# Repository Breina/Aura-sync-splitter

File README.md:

Aura sync splitter
===

Purpose
---
This schematic can be used for when one wants to use the an addressable WS2811B signal to power additional RGB components separately. These component groups will have their own dedicated PSU connection.

Setup
---
Include the `WS2811.lbr` library as a library in Eagle. This is the DIP8 version of the WS2811 IC.

Requirements
---

This board was made in Eagle, so it's a requirement to do anything with the source files. As for hardware, for one board, one needs:
* 8x WS2811 IC's, DIP8 format
* 9x 2.54 mm groups of 4 round pins.
* 9x 33 Ω resistors (R1 - R9) used to prevent reflection and hot-swap.
* 8x 100 nF capacitors used as bypass.
* Every connected component requires an additional resistor (RR0 - RR7). A 330 Ω  resistor should do, but these can be calculated as described in the included WS2811 datasheet, page 5.
* For easy connecting, a 4-pin male molex connection would be handy.

Usage
---

After everything is soldered, the 8 ports can be used to connect Aura Sync headers. The DATA_IN pins are to be connected to the motherboard's addressable LED pins and The molex goes to the PSU.

If more RGB is desired, one can use the DATA_OUT to chain these boards or to use the addressable RGB signal to a final component.

WARNING: Do not make mistakes. The two kinds of Aura headers are exactly the same, mixing them up may cause component failure. Triple check the PSU cables as well and measure the voltages before connecting the motherboard. Wrongly connecting those may damage your motherboard.

Known issues
---
* Aura sync headers are a little larger than there is room for on the board. One can safely sand away a little bit of plastic to make it fit.
* Some addressable RGB headers don't have a hole for a dummy PIN. If using 4 PINs at the DATA_OUT header, you can safely remove the unused one (2nd from the left).

Versions
---
1.1: Fixed the color PIN order. ASUS uses the WS2811B which uses GRB instead of our WS2811's RGB. Also made some more room to solder the resistor.
1.0: Initial version

Disclaimer
---
Use at your own risk. If anything breaks, one only has himself to blame.

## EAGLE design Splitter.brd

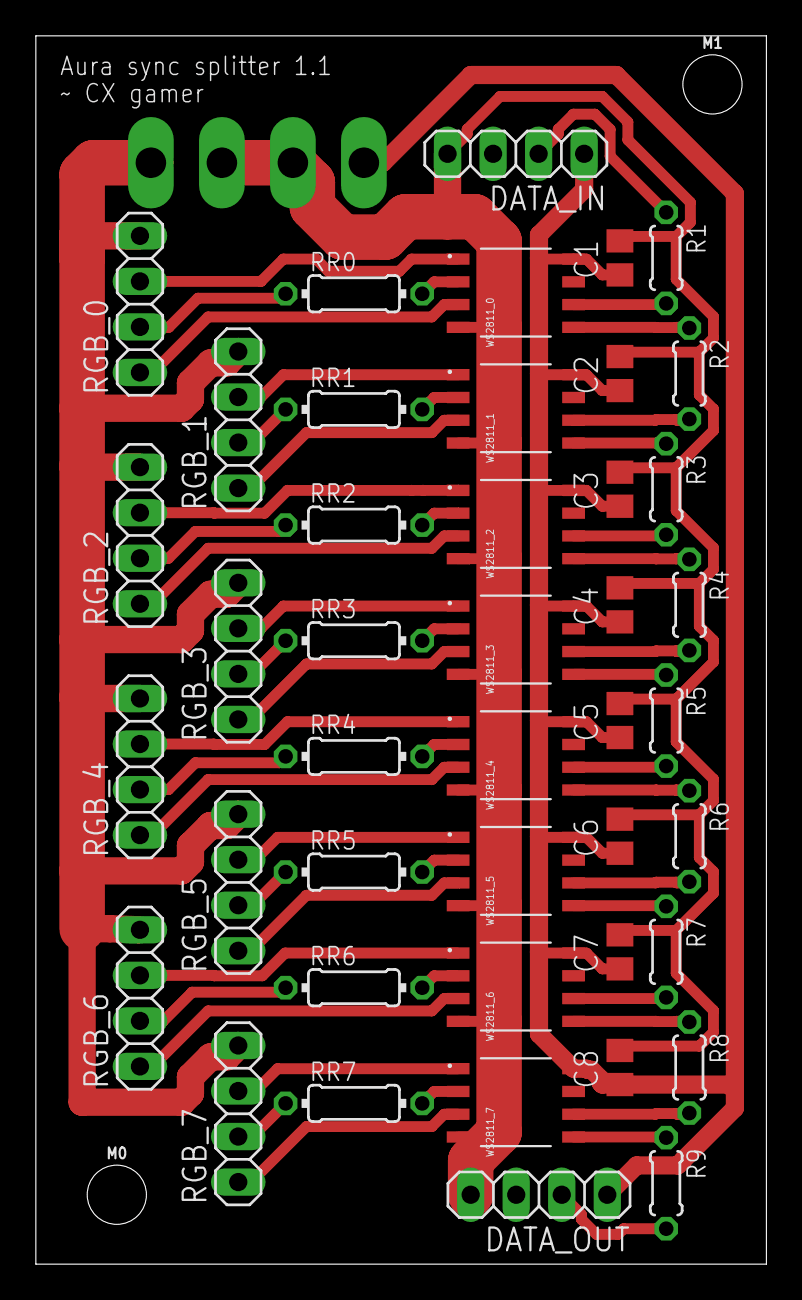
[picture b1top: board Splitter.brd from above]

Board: 2 copper layers, 40.7 x 68.5 mm, 46 parts (1 on the bottom side), 53 nets.

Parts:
C1, C2, C3, C4, C5, C6, C7, C8: 100nF; C0805
DATA_IN: DATA_IN; 1X04
DATA_OUT: DATA_OUT; 1X04
M0, M1: STAND-OFF
POWER: POWER; KK-156-4
R1, R2, R3, R4, R5, R6, R7, R8, R9: 33; 0204/5
RGB_0: RGB_0; 1X04
RGB_1: RGB_1; 1X04
RGB_2: RGB_2; 1X04
RGB_3: RGB_3; 1X04
RGB_4: RGB_4; 1X04
RGB_5: RGB_5; 1X04
RGB_6: RGB_6; 1X04
RGB_7: RGB_7; 1X04
RR0, RR1, RR2, RR3, RR4, RR5, RR6, RR7: 0204/7
WS2811_0: WS2811_0; WS2811
WS2811_1: WS2811_1; WS2811
WS2811_2: WS2811_2; WS2811
WS2811_3: WS2811_3; WS2811
WS2811_4: WS2811_4; WS2811
WS2811_5: WS2811_5; WS2811
WS2811_6: WS2811_6; WS2811
WS2811_7: WS2811_7; WS2811

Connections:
12V: POWER.4, RGB_0.4, RGB_1.4, RGB_2.4, RGB_3.4, RGB_4.4, RGB_5.4, RGB_6.4, RGB_7.4
+5V: R8.2, WS2811_7.DIN
B0: RGB_0.1, WS2811_0.OUTB
B1: RGB_1.1, WS2811_1.OUTB
B2: RGB_2.1, WS2811_2.OUTB
B3: RGB_3.1, WS2811_3.OUTB
B4: RGB_4.1, WS2811_4.OUTB
B5: RGB_5.1, WS2811_5.OUTB
B6: RGB_6.1, WS2811_6.OUTB
B7: RGB_7.1, WS2811_7.OUTB
DO: DATA_OUT.2, R9.2
G0: RGB_0.3, WS2811_0.OUTR
G1: RGB_1.3, WS2811_1.OUTR
G2: RGB_2.3, WS2811_2.OUTR
G3: RGB_3.3, WS2811_3.OUTR
G4: RGB_4.3, WS2811_4.OUTR
G5: RGB_5.3, WS2811_5.OUTR
G6: RGB_6.3, WS2811_6.OUTR
G7: RGB_7.3, WS2811_7.OUTR
GND: C1.2, C2.2, C3.2, C4.2, C5.2, C6.2, C7.2, C8.2, DATA_IN.4, DATA_OUT.4, POWER.2, POWER.3, WS2811_0.GND, WS2811_1.GND, WS2811_2.GND, WS2811_3.GND, WS2811_4.GND, WS2811_5.GND, WS2811_6.GND, WS2811_7.GND
unnamed: R9.1, WS2811_7.DO
unnamed: R2.1, WS2811_0.DO
unnamed: R3.1, WS2811_1.DO
unnamed: R2.2, WS2811_1.DIN
unnamed: R4.1, WS2811_2.DO
unnamed: R6.1, WS2811_4.DO
unnamed: R3.2, WS2811_2.DIN
unnamed: R7.1, WS2811_5.DO
unnamed: R8.1, WS2811_6.DO
unnamed: R4.2, WS2811_3.DIN
unnamed: R5.1, WS2811_3.DO
unnamed: R5.2, WS2811_4.DIN
unnamed: R6.2, WS2811_5.DIN
unnamed: DATA_IN.2, R1.1
unnamed: R7.2, WS2811_6.DIN
R0: RGB_0.2, RR0.1
R1: RGB_1.2, RR1.1
R2: RGB_2.2, RR2.1
R3: RGB_3.2, RR3.1
R4: RGB_4.2, RR4.1
R5: RGB_5.2, RR5.1
R6: RGB_6.2, RR6.1
R7: RGB_7.2, RR7.1
S$4: R1.2, WS2811_0.DIN
S$5: RR0.2, WS2811_0.OUTG
S$6: RR2.2, WS2811_2.OUTG
S$7: RR3.2, WS2811_3.OUTG
S$9: RR1.2, WS2811_1.OUTG
S$10: RR4.2, WS2811_4.OUTG
S$11: RR5.2, WS2811_5.OUTG
S$13: RR6.2, WS2811_6.OUTG
S$14: RR7.2, WS2811_7.OUTG
VCC: C1.1, C2.1, C3.1, C4.1, C5.1, C6.1, C7.1, C8.1, DATA_IN.1, DATA_OUT.1, POWER.1, WS2811_0.VDD, WS2811_1.VDD, WS2811_2.VDD, WS2811_3.VDD, WS2811_4.VDD, WS2811_5.VDD, WS2811_6.VDD, WS2811_7.VDD

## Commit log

2018-05-30 Formatting
2018-05-30 Reduced unclarity
2018-08-01 More documentation and upgraded the board to version 1.1
2018-08-01 Added newline and fixed image rendering error

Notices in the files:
parts and their libraries:
SparkFun-Hardware: Licensing: Creative Commons ShareAlike 4.0 International - https://creativecommons.org/licenses/by-sa/4.0
